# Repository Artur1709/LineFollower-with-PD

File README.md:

# Full LineFollower project including software and designed PCB in EAGLE and STM32Cube

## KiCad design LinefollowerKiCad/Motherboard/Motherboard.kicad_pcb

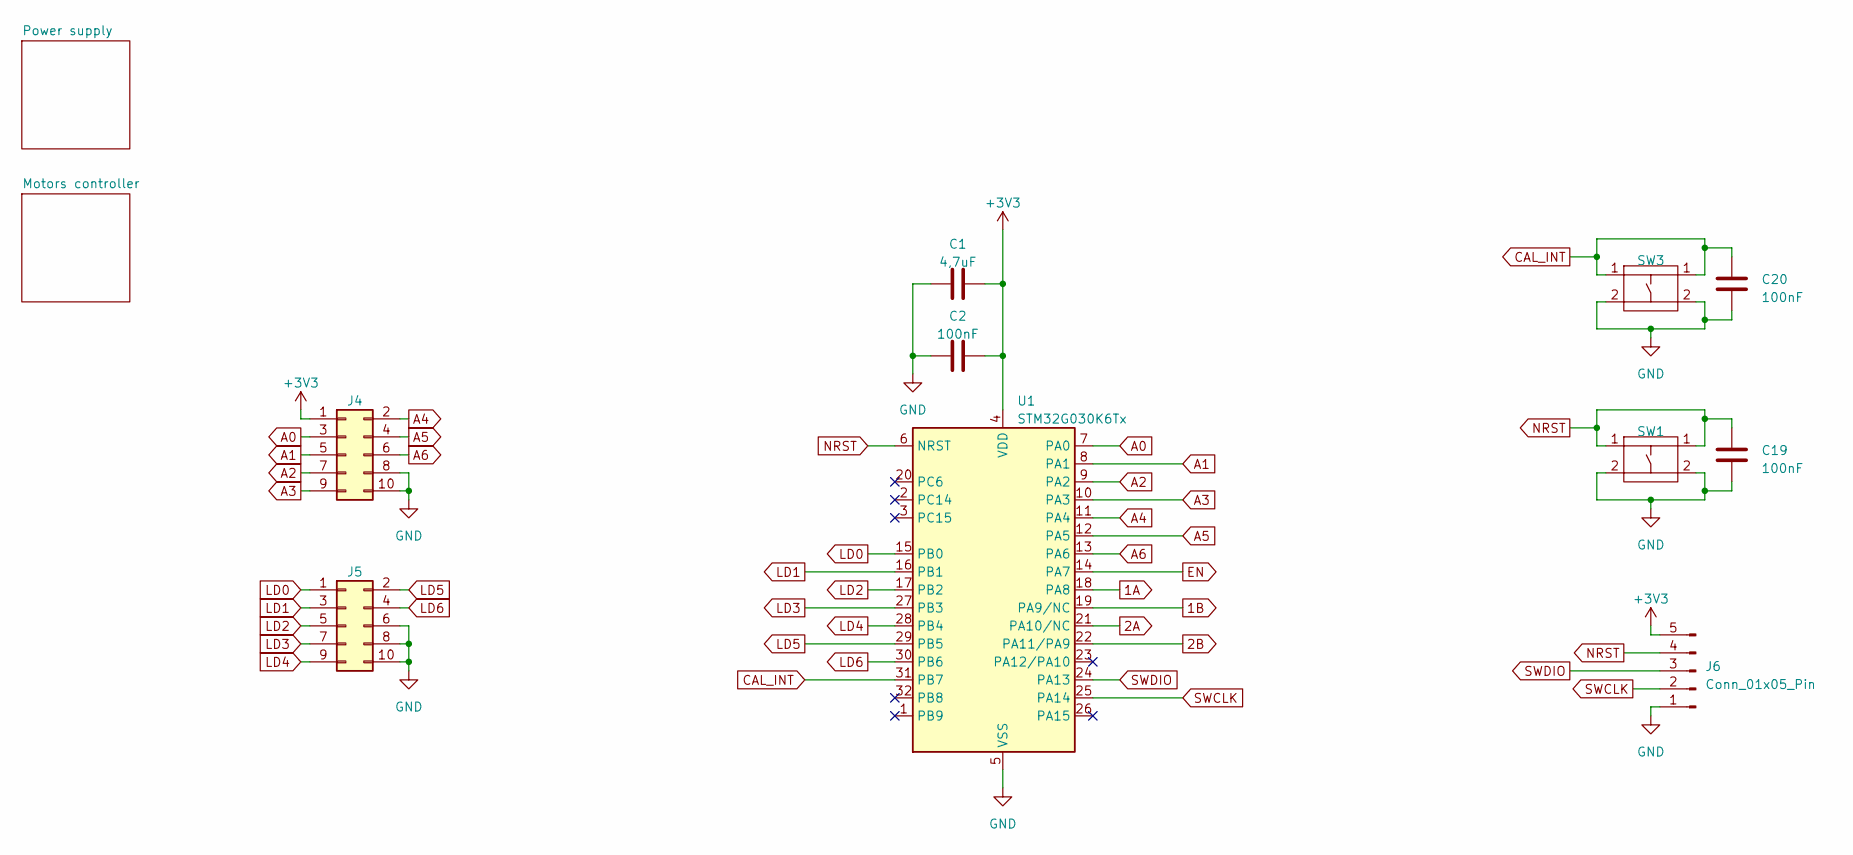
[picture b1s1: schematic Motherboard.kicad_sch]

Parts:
C1: 4,7uF; C_1206_3216Metric
C2, C19, C20: 100nF; C_1206_3216Metric
J4, J5: Conn_02x05_Odd_Even; IDC-Header_2x05_P2.54mm_Vertical
J6: Conn_01x05_Pin; PinHeader_1x05_P2.54mm_Vertical
SW1, SW3: SW_PUSH_6mm
U1: STM32G030K6Tx; LQFP-32_7x7mm_P0.8mm

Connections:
1A: U1.18 (PA8); also elsewhere on the board
1B: U1.19 (PA9/NC); also elsewhere on the board
2A: U1.21 (PA10/NC); also elsewhere on the board
2B: U1.22 (PA11/PA9); also elsewhere on the board
+3V3: C1.2, C2.2, J4.1, J6.5, U1.4 (VDD); also elsewhere on the board
A0: J4.3, U1.7 (PA0)
A1: J4.5, U1.8 (PA1)
A2: J4.7, U1.9 (PA2)
A3: J4.9, U1.10 (PA3)
A4: J4.2, U1.11 (PA4)
A5: J4.4, U1.12 (PA5)
A6: J4.6, U1.13 (PA6)
CAL_INT: C20.2, SW3.1, U1.31 (PB7)
EN: U1.14 (PA7); also elsewhere on the board
GND: C1.1, C2.1, C19.1, C20.1, J4.8, J4.10, J5.6, J5.8, J5.10, J6.1, SW1.2, SW3.2, U1.5 (VSS); also elsewhere on the board
LD0: J5.1, U1.15 (PB0)
LD1: J5.3, U1.16 (PB1)
LD2: J5.5, U1.17 (PB2)
LD3: J5.7, U1.27 (PB3)
LD4: J5.9, U1.28 (PB4)
LD5: J5.2, U1.29 (PB5)
LD6: J5.4, U1.30 (PB6)
NRST: C19.2, J6.4, SW1.1, U1.6 (NRST)
SWCLK: J6.2, U1.25 (PA14)
SWDIO: J6.3, U1.24 (PA13)

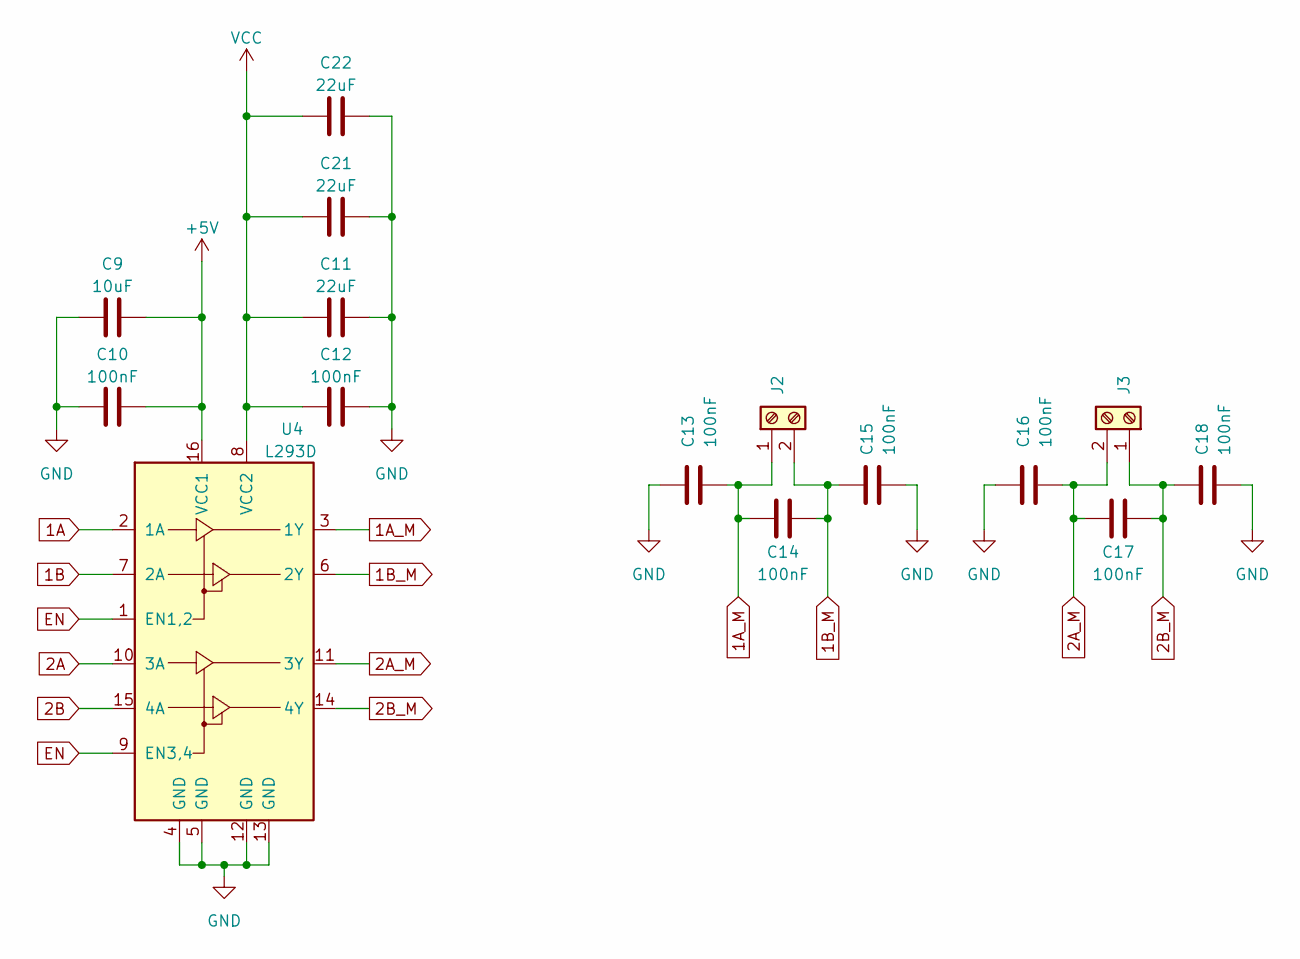
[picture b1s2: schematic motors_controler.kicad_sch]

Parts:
C9: 10uF; C_1206_3216Metric
C10, C12, C13, C14, C15, C16, C17, C18: 100nF; C_1206_3216Metric
C11, C21, C22: 22uF; C_1206_3216Metric
J2, J3: Screw_Terminal_01x02; Pollolu_motor_goldpin
U4: L293D; DIP-16_W7.62mm

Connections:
1A: U4.2 (1A); also elsewhere on the board
1A_M: C13.2, C14.2, J2.1, U4.3 (1Y)
1B: U4.7 (2A); also elsewhere on the board
1B_M: C14.1, C15.1, J2.2, U4.6 (2Y)
2A: U4.10 (3A); also elsewhere on the board
2A_M: C16.2, C17.2, J3.2, U4.11 (3Y)
2B: U4.15 (4A); also elsewhere on the board
2B_M: C17.1, C18.1, J3.1, U4.14 (4Y)
+5V: C9.2, C10.2, U4.16 (VCC1); also elsewhere on the board
EN: U4.1 (EN1,2), U4.9 (EN3,4); also elsewhere on the board
GND: C9.1, C10.1, C11.2, C12.2, C13.1, C15.2, C16.1, C18.2, C21.2, C22.2, U4.4 (GND), U4.5 (GND), U4.12 (GND), U4.13 (GND); also elsewhere on the board
VCC: C11.1, C12.1, C21.1, C22.1, U4.8 (VCC2); also elsewhere on the board

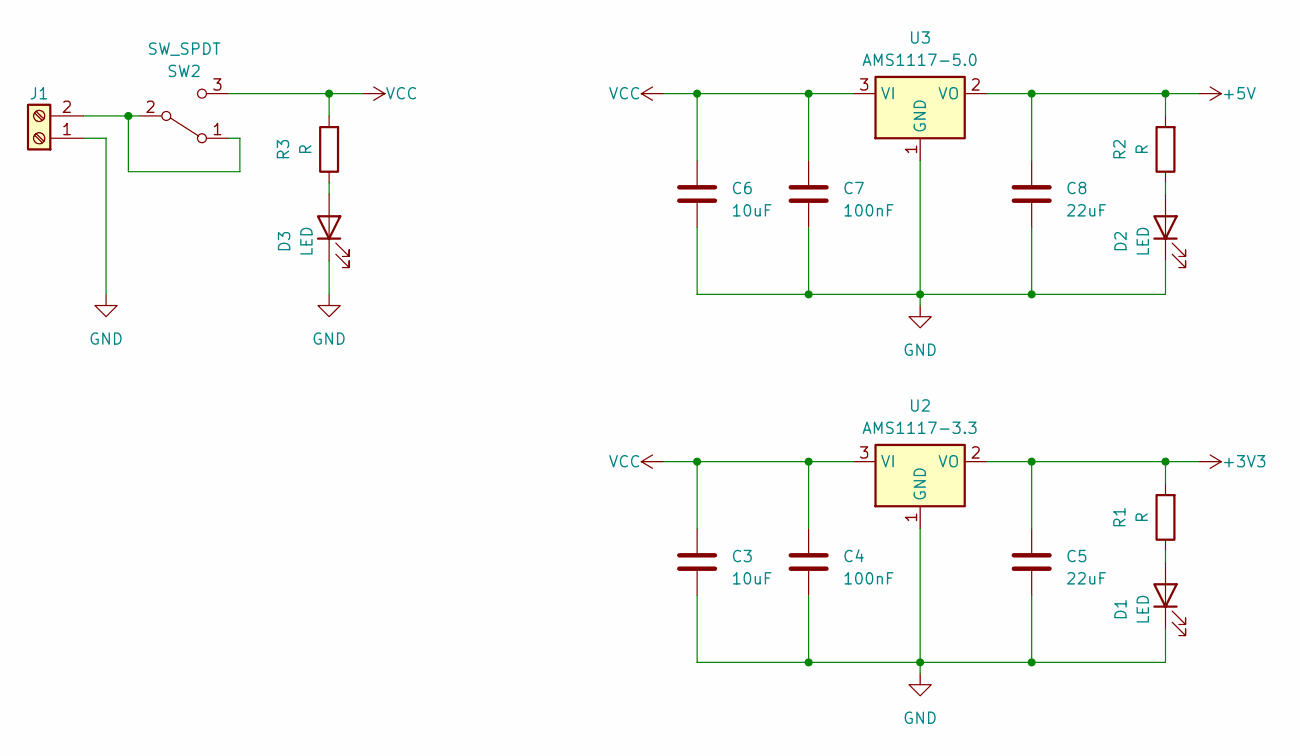
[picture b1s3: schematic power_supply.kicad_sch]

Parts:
C3, C6: 10uF; C_1206_3216Metric
C4, C7: 100nF; C_1206_3216Metric
C5, C8: 22uF; C_1206_3216Metric
D1, D2, D3: LED; LED_1210_3225Metric_Pad1.42x2.65mm_HandSolder
J1: Screw_Terminal_01x02; AMASS_XT60-M_1x02_P7.20mm_Vertical
R1, R2, R3: R; R_1206_3216Metric
SW2: SW_SPDT; SPDT_5MS1S102AM6QE
U2: AMS1117-3.3; SOT-223-3_TabPin2
U3: AMS1117-5.0; SOT-223-3_TabPin2

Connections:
+3V3: C5.1, R1.2, U2.2 (VO); also elsewhere on the board
+5V: C8.1, R2.2, U3.2 (VO); also elsewhere on the board
GND: C3.2, C4.2, C5.2, C6.2, C7.2, C8.2, D1.1 (K), D2.1 (K), D3.1 (K), J1.1, U2.1 (GND), U3.1 (GND); also elsewhere on the board
unnamed: D1.2 (A), R1.1
unnamed: D2.2 (A), R2.1
unnamed: D3.2 (A), R3.1
unnamed: J1.2, SW2.1 (A), SW2.2 (B)
VCC: C3.1, C4.1, C6.1, C7.1, R3.2, SW2.3 (C), U2.3 (VI), U3.3 (VI); also elsewhere on the board

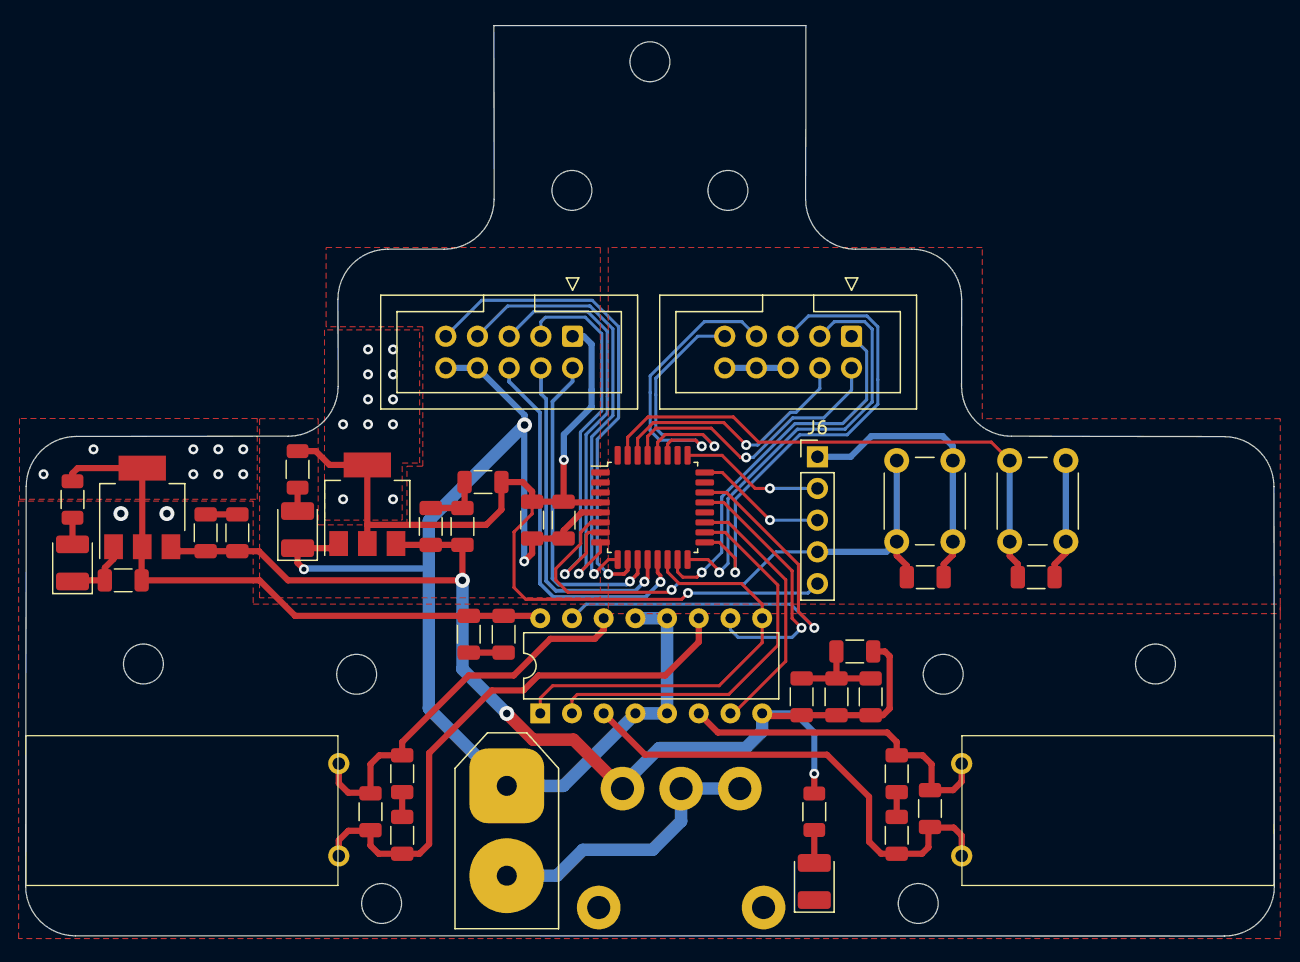
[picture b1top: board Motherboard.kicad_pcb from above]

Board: 2 copper layers, 100.1 x 72.9 mm, 41 parts (0 on the bottom side), 35 nets.

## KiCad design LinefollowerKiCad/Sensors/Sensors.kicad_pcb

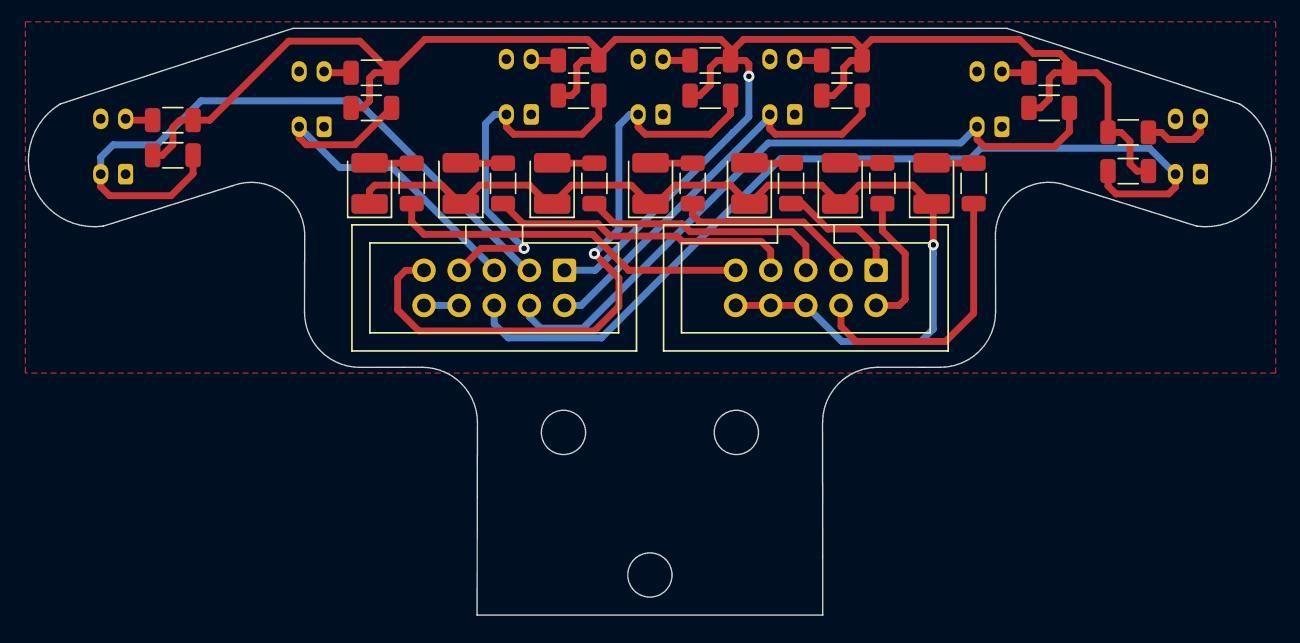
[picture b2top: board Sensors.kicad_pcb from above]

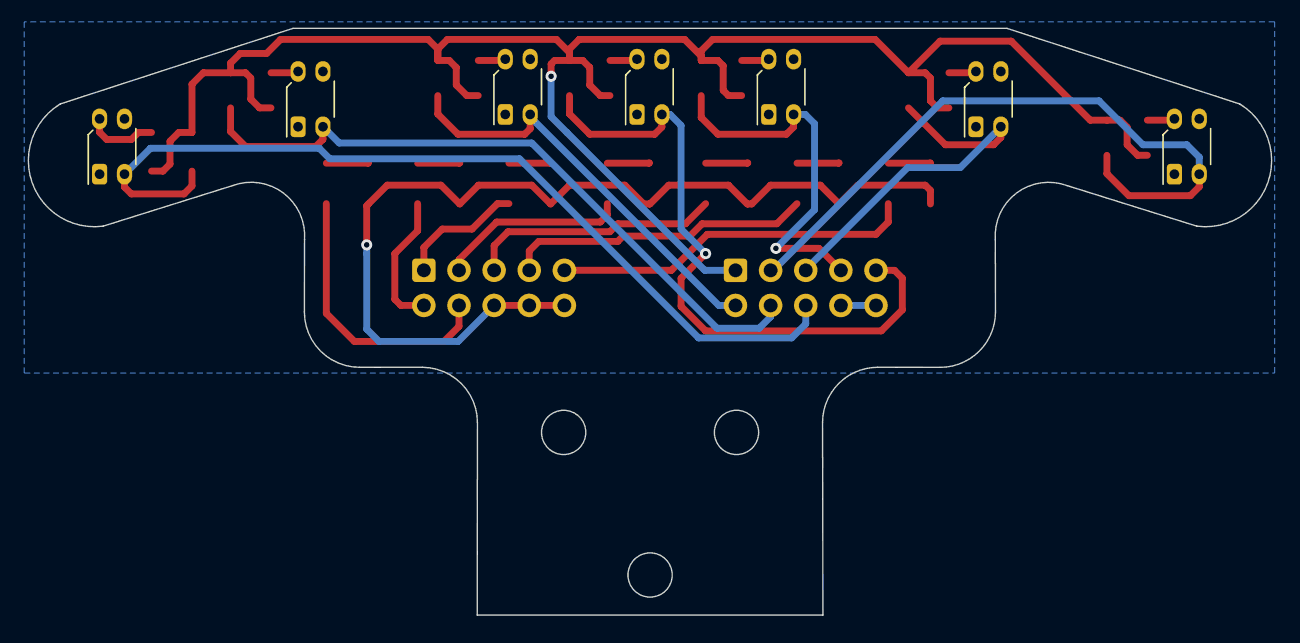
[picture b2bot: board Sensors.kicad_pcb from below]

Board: 2 copper layers, 89.9 x 42.4 mm, 37 parts (7 on the bottom side), 31 nets.

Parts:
D1, D2, D3, D4, D5, D6, D7: LED; LED_1210_3225Metric_Pad1.42x2.65mm_HandSolder
J2, J4: Conn_02x05_Odd_Even; IDC-Header_2x05_P2.54mm_Vertical
R1, R2, R3, R4, R5, R6, R7, R8, R9, R10, R11, R12, R13, R14, R15, R16, R17, R18, R19, R20, R21: R; R_1206_3216Metric
U1, U2, U3, U4, U5, U6, U7: ITR8307-F43; Everlight_ITR8307F43

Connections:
+3V3: J2.1, R1.1, R2.1, R3.1, R4.1, R5.1, R6.1, R7.1, R8.1, R9.1, R10.1, R11.1, R12.1, R13.1, R14.1
A0_C: J2.3, R3.2, U1.3 (C)
A1_C: J2.5, R7.2, U2.3 (C)
A2_C: J2.7, R11.2, U3.3 (C)
A3_C: J2.9, R14.2, U4.3 (C)
A4_C: J2.2, R4.2, U5.3 (C)
A5_C: J2.4, R8.2, U6.3 (C)
A6_C: J2.6, R12.2, U7.3 (C)
GND: J2.8, J2.10, U1.1 (K), U1.4 (E), U2.1 (K), U2.4 (E), U3.1 (K), U3.4 (E), U4.1 (K), U4.4 (E), U5.1 (K), U5.4 (E), U6.1 (K), U6.4 (E), U7.1 (K), U7.4 (E)
GND1: D1.1 (K), D2.1 (K), D3.1 (K), D4.1 (K), D5.1 (K), D6.1 (K), D7.1 (K), J4.6, J4.8, J4.10
LD0_C: J4.1, R19.2
LD1_C: J4.3, R18.2
LD2_C: J4.5, R17.2
LD3_C: J4.7, R16.2
LD4_C: J4.9, R15.2
LD5_C: J4.2, R20.2
LD6_C: J4.4, R21.2
unnamed: D1.2 (A), R15.1
unnamed: D2.2 (A), R16.1
unnamed: D3.2 (A), R17.1
unnamed: D4.2 (A), R18.1
unnamed: D5.2 (A), R19.1
unnamed: D6.2 (A), R20.1
unnamed: D7.2 (A), R21.1
unnamed: R1.2, U1.2 (A)
unnamed: R5.2, U2.2 (A)
unnamed: R9.2, U3.2 (A)
unnamed: R13.2, U4.2 (A)
unnamed: R2.2, U5.2 (A)
unnamed: R6.2, U6.2 (A)
unnamed: R10.2, U7.2 (A)

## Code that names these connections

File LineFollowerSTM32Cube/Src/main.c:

#include <stdint.h>
#include "stm32g030xx.h"
// Definicje makr dla wlaczania i wylaczania diod oraz threshold
#define LD0_ON GPIOB->BSRR |= GPIO_BSRR_BS4
#define LD1_ON GPIOB->BSRR |= GPIO_BSRR_BS3
#define LD2_ON GPIOB->BSRR |= GPIO_BSRR_BS2
#define LD3_ON GPIOB->BSRR |= GPIO_BSRR_BS1
#define LD4_ON GPIOB->BSRR |= GPIO_BSRR_BS0
#define LD5_ON GPIOB->BSRR |= GPIO_BSRR_BS5
#define LD6_ON GPIOB->BSRR |= GPIO_BSRR_BS6

#define LD0_OFF GPIOB->BSRR |= GPIO_BSRR_BR4
#define LD1_OFF GPIOB->BSRR |= GPIO_BSRR_BR3
#define LD2_OFF GPIOB->BSRR |= GPIO_BSRR_BR2
#define LD3_OFF GPIOB->BSRR |= GPIO_BSRR_BR1
#define LD4_OFF GPIOB->BSRR |= GPIO_BSRR_BR0
#define LD5_OFF GPIOB->BSRR |= GPIO_BSRR_BR5
#define LD6_OFF GPIOB->BSRR |= GPIO_BSRR_BR6

// Definicja wartosci ADC wykrywajaca linie
#define threshold 4050

// Definicja funkcji wykorzystywanych w dalszej czesci kodu
void LED_init(void); // funkcja do zainicjalizowania wyjsc mikrokontrolera do sterowania Diodami;
void LED_set(void);  // funkcja zalaczajaca diody led informujace o wykryciu czarnej linii
void ADC_init(void); // funkcja inicjalizujaca piny na konwerter analogowo cyfrowy do odczytywania wartosci z, czujnikow
void ADC_enable(void); // funkcja zalaczajaca konwerter analogowo cyfrowy do odczytywania wartosci z czujnikww
uint32_t ADC_read(uint32_t channel); // funkcja odczytujaca wartosci z konkretnych czujnikow podlaczonych do mikrokontrolera (channel od 0-7)
void PWM_init(void); // funkcja inicjalizujaca piny na wyjscie sygnalu PWM
void PWM1_set(uint16_t pwmValue); // funkcja ustawiajaca wyjscie na konkretna wartosc wypelnienia sygnalu PWM
void PWM2_set(uint16_t pwmValue); // funkcja ustawiajaca wyjscie na konkretna wartosc wypelnienia sygnalu PWM
void LD293_init(void); // funkcja inicjalizujaca pinow kontrolera podlaczonego do silnikow

int main(void) {
	LED_init();
	ADC_init();
	PWM_init();
	LD293_init();
	ADC_enable();
	// Czlon proporcjonalny, wartosc dobrana testowo
	int Kp = 200;
	// Czlon rozniczkujacy, wartosc dobrana testowo
	int Kd = 120;
	// Etykieta przypisywana czujnikowi gdy wykryje linie
	int error = 0;
	// Aktualna etykieta przy wykryciu linii przez czujnik
	int current_error = 0;
	// Zmienna sluzaca do obliczenia rozniczki
	int derivative = 0;
	// Poprzednia etykieta przy wykryciu linii przez czujnik
	int previous_error = 0;



	/* Glowna petla programu */
	while (1) {
		LED_set();
// Wartosc threshold zostala obliczona ze wzoru z dokumentacji
//na podstawie zmierzonego napiecia z czujnika podczas przylozenia go do czarnej linii
		if (ADC_read(0) > threshold)
			error = -5;
		else if (ADC_read(1) > threshold)
			error = -3;
		else if (ADC_read(2) > threshold)
			error = -2;
		else if (ADC_read(3) > threshold)
			error = 0;
		else if (ADC_read(4) > threshold)
			error = 2;
		else if (ADC_read(5) > threshold)
			error = 3;
		else if (ADC_read(6) > threshold)
			error = 5;

		current_error = error;
		derivative = current_error - previous_error;

		uint16_t PWM_left = 0;
		uint16_t PWM_right = 0;
// Sprawdzenie z ktorej strony czujnik wykryl linie
		if(current_error>0){
// Odejmowanie regulatora PD
			PWM_left = 900 - ((Kp*error) + (Kd*derivative));
// Blokada przed przekroczeniem max wartosci PWM
			if(PWM_left >= 999)
				PWM_left = 999;

			PWM_right = 900;
// Blokada przed przekroczeniem max wartosci PWM
			if(PWM_right >= 999)
				PWM_right = 999;
		}
		else{
			PWM_left = 900;
			if(PWM_left >= 999)
				PWM_left = 999;
// Dodawanie regulatora PD
			PWM_right = 900 + ((Kp*error) + (Kd*derivative));
			if(PWM_right >= 999)
				PWM_right = 999;
		}
// Przekazywanie obliczonych parametrow do funkcji
		PWM1_set(PWM_left);
		PWM2_set(PWM_right);
		previous_error = current_error;

	}
}

void LED_init() {

// Wlaczenie zegara dla portu B
	RCC->IOPENR |= RCC_IOPENR_GPIOBEN;
// Ustawienie pinow dla diod jako wyjscia, aby zapalic je w potrzebnym momencie
	GPIOB->MODER &= ~GPIO_MODER_MODE0_1;
	GPIOB->MODER &= ~GPIO_MODER_MODE1_1;
	GPIOB->MODER &= ~GPIO_MODER_MODE2_1;
	GPIOB->MODER &= ~GPIO_MODER_MODE3_1;
	GPIOB->MODER &= ~GPIO_MODER_MODE4_1;
	GPIOB->MODER &= ~GPIO_MODER_MODE5_1;
	GPIOB->MODER &= ~GPIO_MODER_MODE6_1;

}

void ADC_init() {
// Wlaczenie zegara dla portu A
	RCC->IOPENR |= RCC_IOPENR_GPIOAEN;
// Wlaczenie zegara dla modulu ADC
	RCC->APBENR2 |= RCC_APBENR2_ADCEN;


}

void ADC_enable() {
// Wlaczenie gotowosci ADC
	ADC1->ISR |= ADC_ISR_ADRDY;
// Wlaczenie modulu ADC
	ADC1->CR |= ADC_CR_ADEN;
// Oczekiwanie na gotowosc ADC
	while ((ADC1->ISR & ADC_ISR_ADRDY) == 0);

}
uint32_t ADC_read(uint32_t channel) {
// Wybor kanalu ADC, aby zarejestrowac odczyt z danego czujnika
	ADC1->CHSELR = (1 << channel);
// Start konwersji na wartosc cyfrowa
	ADC1->CR |= ADC_CR_ADSTART;
// Oczekiwanie na zakonczenie konwersji
	while ((ADC1->ISR & ADC_ISR_EOC) == 0);
// Zwrocenie wyniku
	return ADC1->DR;

}

void PWM_init(void) {
// Wlacz zegar dla portu A
	RCC->IOPENR |= RCC_IOPENR_GPIOAEN;

// Wlacz zegar dla timera 1
	RCC->APBENR2 |= RCC_APBENR2_TIM1EN;

// Konfiguracja pinow jako wyjscia alternatywne ( alternate function mode)
	GPIOA->MODER &= ~(GPIO_MODER_MODE9_0); // Wyczyszenie poprzednich ustawien bitow
	GPIOA->MODER &= ~(GPIO_MODER_MODE11_0);
	GPIOA->MODER |= (GPIO_MODER_MODE9_1); // Ustawienie jedynek na konkertnych bitach
	GPIOA->MODER |= (GPIO_MODER_MODE11_1);
// Podpiecie pinow do poszczegolnych kanalow
// TIM1_CH2 PA9, pin lewego silnika na ktory jest wysylany sygnal PWM
	GPIOA->AFR[1] |= GPIO_AFRH_AFSEL9_1;
// TIM1_CH2 PA11, pin prawego silnika na ktory jest wysylany sygnal PWM
	GPIOA->AFR[1] |= GPIO_AFRH_AFSEL11_1;
// Ustawienie PA8 i PA10 jako wyjscia
	GPIOA->MODER &= ~GPIO_MODER_MODE8_1;
	GPIOA->MODER &= ~GPIO_MODER_MODE10_1;
// Ustawienie logicznego 0 na pinach PA8 i PA9
// W taki sposob uzyskujemy na pinach mase co pozwala na prawidłowy kierunek obrotu silnikow
	GPIOA->BSRR |= GPIO_BSRR_BR8;
	GPIOA->BSRR |= GPIO_BSRR_BR10;

// Konfiguracja timera TIM1
	TIM1->CR1 &= ~TIM_CR1_DIR; // Kierunek zliczania w gore
	TIM1->CR1 &= ~TIM_CR1_CMS; // Tryb zliczania w gore
	TIM1->PSC = 15;             // Prescaler
	TIM1->ARR = 999;           // Wartosc autoreload (maksymalny zakres PWM)
// Wlaczenie glownego sygnalu TIM1
	TIM1 -> BDTR |= TIM_BDTR_MOE;
// Konfiguracja kanalow PWM
	TIM1->CCMR1 |= TIM_CCMR1_OC2M_1 | TIM_CCMR1_OC2M_2 | TIM_CCMR1_OC2PE; // Tryb PWM1 na kanale 2
	TIM1->CCMR2 |= TIM_CCMR2_OC4M_1 | TIM_CCMR2_OC4M_2 | TIM_CCMR2_OC4PE; // Tryb PWM1 na kanale 4

// Wlaczenie kanalow
	TIM1->CCER |= TIM_CCER_CC2E; // Wlacz kanal 2
	TIM1->CCER |= TIM_CCER_CC4E; // Wlacz kanal 4

// Wlaczenie licznika timera
	TIM1->CR1 |= TIM_CR1_CEN;

// Aktualizowanie generacji
	TIM1 -> EGR |= TIM_EGR_UG;
}
// Funkcja ustawiajaca predkosc lewego kola
void PWM1_set(uint16_t pwmValue) {
// Wartosc PWM dla kanalu 2,ustawienie wypelnienia sygnalu PWM z zakresu wartosci (0-1000),
// 100 to 10% wypelnienia itd
	TIM1->CCR2 = pwmValue;
}
// Funkcja ustawiajaca predkosc prawego kola
void PWM2_set(uint16_t pwmValue) {
// Wartosc PWM dla kanalu 4,ustawienie wypelnienia sygnalu PWM z zakresu wartosci (0-1000),
// 100 to 10% wypelnienia itd
	TIM1->CCR4 = pwmValue;
}
void LD293_init(void) {
// Wlaczenie zegara dla portu A
	RCC->IOPENR |= RCC_IOPENR_GPIOAEN;
// Ustawienie pinu PA7 jako wyjscie
	GPIOA->MODER &= ~(GPIO_MODER_MODE7_1);
// Ustawienie logicznej 1 na pinie PA7. Wlaczenie sterownika od silnikow
	GPIOA -> BSRR |= GPIO_BSRR_BS7;
}

void LED_set(void){
// Wartosc threshold jest powiazana z czujnikami,
// gdy dany czujnik wykryje linie swieci sie takze odpowiednia dioda
	if (ADC_read(0) > threshold) {
		LD0_ON;
	} else
		LD0_OFF;

	if (ADC_read(1) > threshold) {
		LD1_ON;
	} else
		LD1_OFF;

	if (ADC_read(2) > threshold) {
		LD2_ON;
	} else
		LD2_OFF;

	if (ADC_read(3) > threshold) {
		LD3_ON;
	} else
		LD3_OFF;

	if (ADC_read(4) > threshold) {
		LD4_ON;
	} else
		LD4_OFF;

	if (ADC_read(5) > threshold) {
		LD5_ON;
	} else
		LD5_OFF;

	if (ADC_read(6) > threshold) {
		LD6_ON;
	} else
		LD6_OFF;

}

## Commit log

2024-04-22 Added all files of project
